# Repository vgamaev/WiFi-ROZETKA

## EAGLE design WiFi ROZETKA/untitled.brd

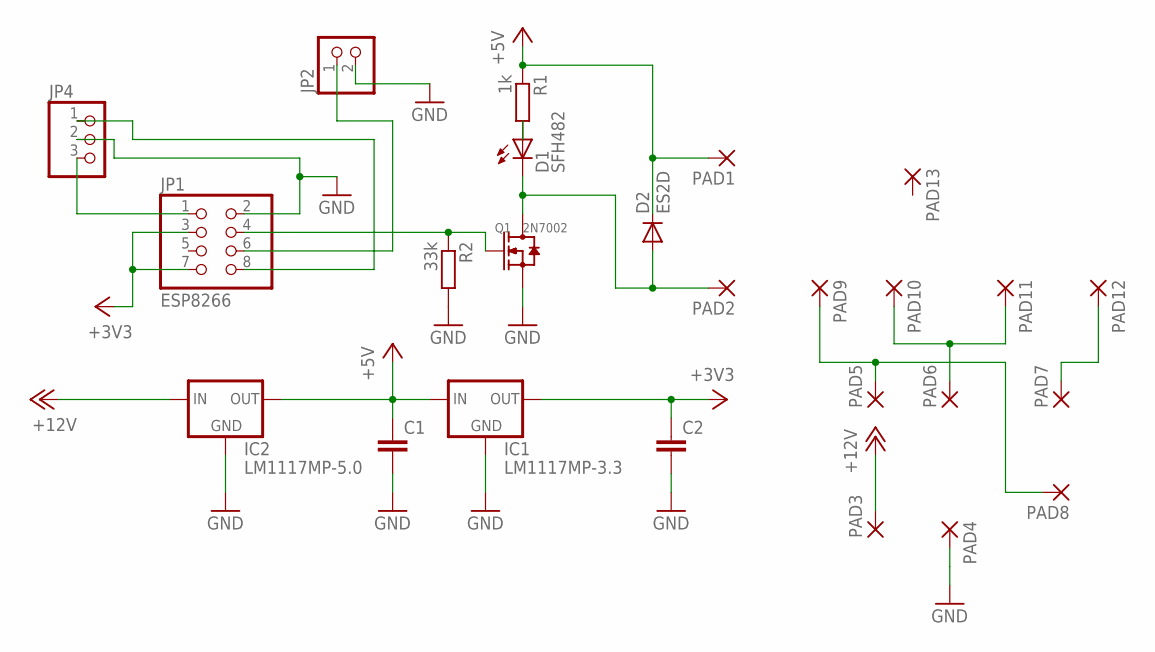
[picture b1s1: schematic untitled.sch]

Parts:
C1, C2: C-EUC1812; C1812
D1: SFH482
D2: ES2D; SMB
IC1: LM1117MP-3.3; SOT223
IC2: LM1117MP-5.0; SOT223
JP1: ESP8266; 2X04
JP2: PINHD-1X2; 1X02
JP4: PINHD-1X3; 1X03
PAD1, PAD2, PAD3, PAD4, PAD5, PAD6, PAD7, PAD8, PAD9, PAD10, PAD11, PAD12, PAD13: 3,17/1,1
Q1: 2N7002; SOT-23
R1: 1k; M0805
R2: 33k; M0805

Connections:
+5V: C1.1, D2.C, IC1.3 (IN), IC2.2 (OUT), IC2.4 (OUT), PAD1.1, R1.1
+12V: IC2.3 (IN), PAD3.1
GND: C1.2, C2.2, IC1.1 (GND), IC2.1 (GND), JP1.2, JP2.2, JP4.2, PAD4.1, Q1.2 (S), R2.2
unnamed: JP1.1, JP4.3
unnamed: JP1.4, Q1.1 (G), R2.1
unnamed: D1.K (C), D2.A, PAD2.1, Q1.3 (D)
unnamed: D1.A, R1.2
unnamed: JP1.8, JP4.1
unnamed: JP1.6, JP2.1
unnamed: PAD5.1, PAD8.1, PAD9.1
unnamed: PAD6.1, PAD10.1, PAD11.1
unnamed: PAD7.1, PAD12.1
unnamed: C2.1, IC1.2 (OUT), IC1.4 (OUT), JP1.3, JP1.7

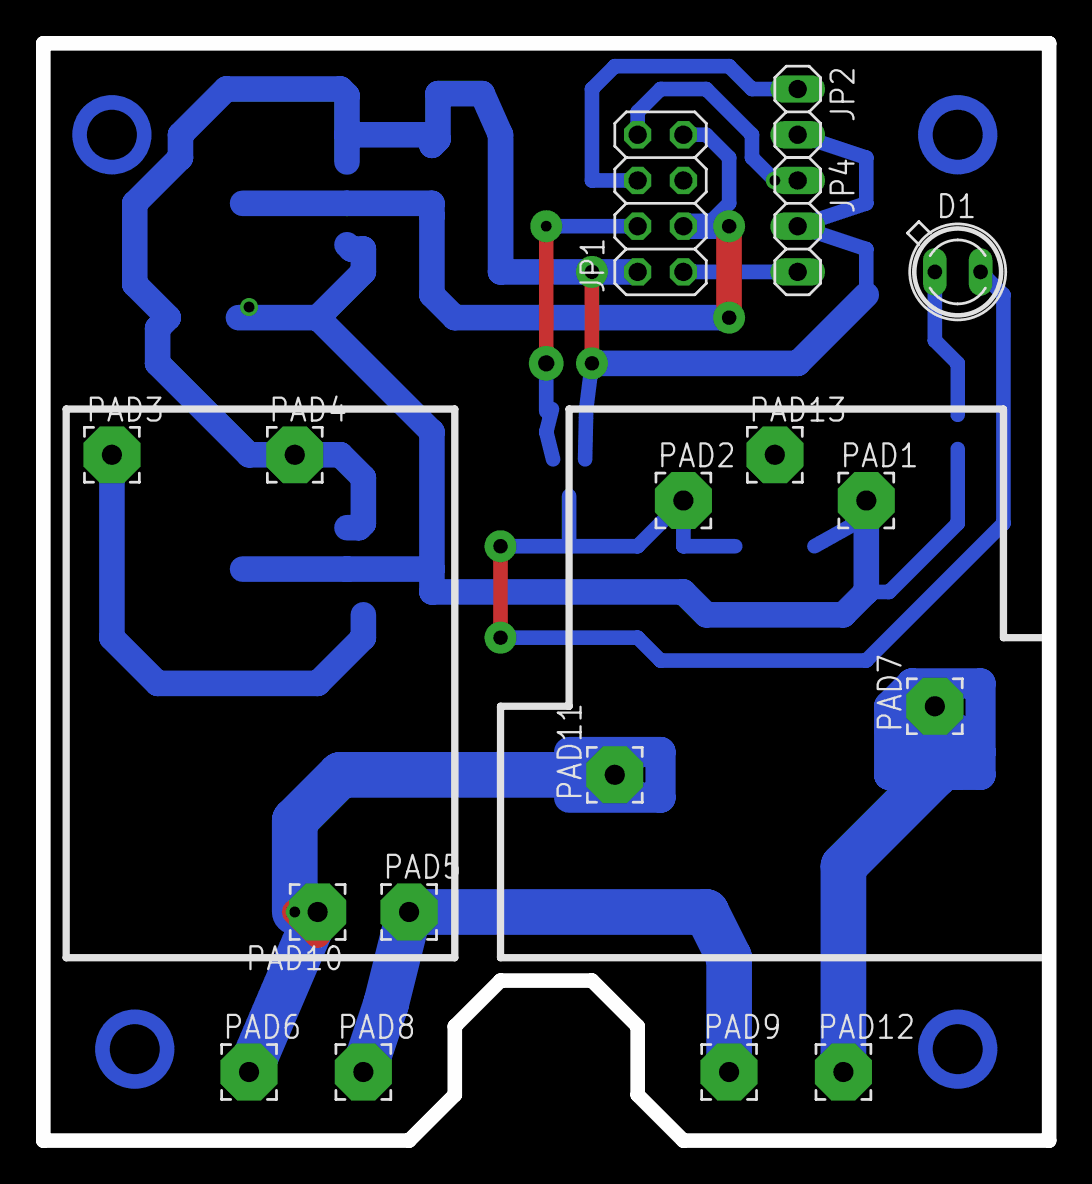
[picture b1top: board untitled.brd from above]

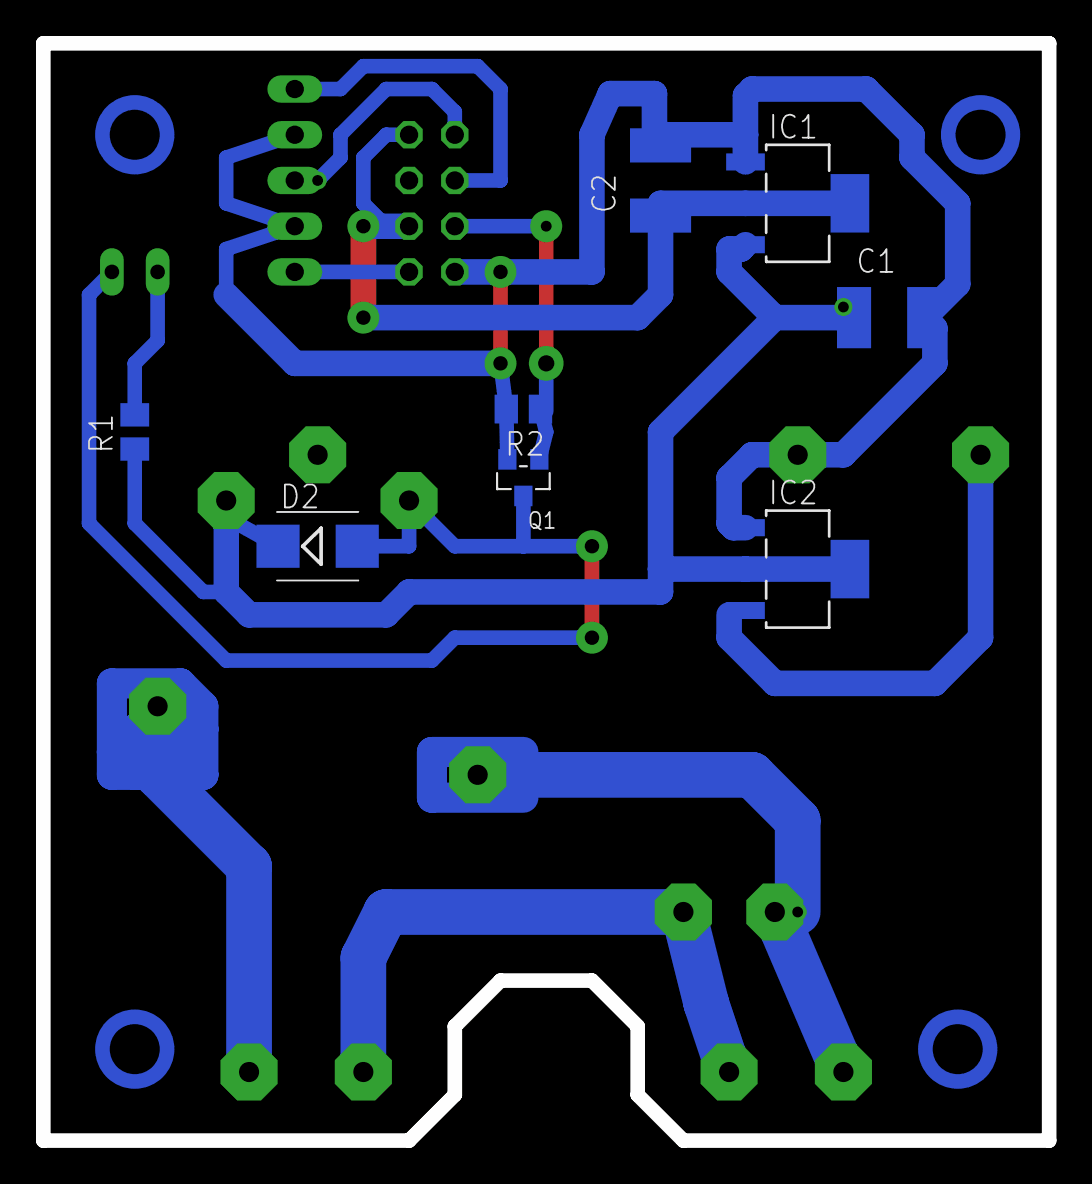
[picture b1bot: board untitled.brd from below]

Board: 2 copper layers, 55.9 x 61.0 mm, 25 parts (8 on the bottom side), 13 nets.

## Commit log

2017-08-26 :boom::camel: Added .gitattributes & .gitignore files
2017-08-26 start
2017-08-26 26082017
2018-02-24 24022018
